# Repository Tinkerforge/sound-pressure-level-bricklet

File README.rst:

Sound Pressure Level Bricklet
=============================

This repository contains the firmware source code and the hardware design
files. The documentation generator configs can be found at
https://github.com/Tinkerforge/generators

Repository Content
------------------

software/:
 * examples/: Examples for all supported languages
 * build/: Compiled files
 * src/: Source code of firmware
 * Makefile: Makefile to build project

hardware/:
 * Contains KiCad project files and additionally schematics as PDF

datasheets/:
 * Contains datasheets for sensors and complex ICs that are used

Hardware
--------

The hardware is designed with the open source EDA Suite KiCad
(http://www.kicad.org). Before you are able to open the files,
you have to install the Tinkerforge kicad-libraries
(https://github.com/Tinkerforge/kicad-libraries). You can either clone
them directly in hardware/ or clone them in a separate folder and
symlink them into hardware/
(ln -s kicad_path/kicad-libraries project_path/hardware). After that you
can open the .pro file in hardware/ with KiCad and from there view and
modify the schematics and the PCB layout.

Software
--------

If you want to do your own Brick/Bricklet firmware development we highly
recommend that you use our build environment setup script and read the
tutorial (https://www.tinkerforge.com/en/doc/Tutorials/Tutorial_Build_Environment/Tutorial.html).

To compile the C code we recommend you to install the newest GNU Arm Embedded
Toolchain (https://launchpad.net/gcc-arm-embedded/+download).
You also need to install bricklib2 (https://github.com/Tinkerforge/bricklib2).

You can either clone it directly in software/src/ or clone it in a
separate folder and symlink it into software/src/
(ln -s bricklib_path/bricklib2 project_path/software/src/). Finally make sure to
have CMake installed (http://www.cmake.org/cmake/resources/software.html).

After that you can build the firmware by invoking make in software/.
The firmware (.zbin) can then be found in software/build/ and uploaded
with brickv (click button "Flashing" on start screen).

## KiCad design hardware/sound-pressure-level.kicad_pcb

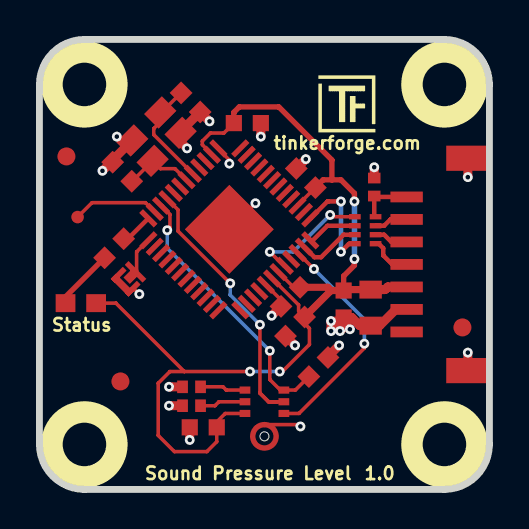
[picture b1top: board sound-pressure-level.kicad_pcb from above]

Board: 2 copper layers, 25.0 x 25.0 mm, 31 parts (2 on the bottom side), 21 nets.

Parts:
C1: 10uF; C0805
C2: 1uF; C0603F
C3, C4, C5, C10: 100nF; C0603F
C6: 220nF; C0603F
C7: 220pF; C0402F
C8, C9: 10pF; C0603F
D3: blue; D0603E
Fiducial_Mark: VAL**; Fiducial_Mark
Fiducial_Mark#2, Fiducial_Mark#3: VAL**; Fiducial_Mark
P1: CON-SENSOR2
P2: BOOT; SolderJumper
P3: DEBUG; DEBUG_PAD
R1: 1k; R0603F
R2: 100k; R0603F
R3, R4: 0; R0402F
RP1: 82; 4X0402
U1: XMC1404; QFN48-EP2
U2, U3, U4, U5: DRILL; DRILL_NP
U6: ICS-43432
VAL: WEEE_7mm
VAL#2: CE_5mm
X1: 16MHz; CRYSTAL_3225

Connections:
GND: C1.1, C2.1, C3.2, C4.2, C5.2, C6.2, C7.2, C8.2, C9.2, C10.1, P1.2, P1.EP, P2.1, R2.2, R3.2, R4.2, U1.17, U1.37, U1.EP, U6.4, X1.3
unnamed: C7.1, P1.7, RP1.4
unnamed: C8.1, U1.41, X1.2
unnamed: C9.1, U1.42, X1.1
unnamed: D3.2, R1.2
unnamed: P1.4, RP1.1
unnamed: P1.5, RP1.2
unnamed: P1.6, RP1.3
unnamed: P2.2, U1.1
unnamed: P3.1, U1.47
unnamed: R1.1, U1.48
unnamed: R3.1, U6.1
unnamed: R4.1, U6.2
S-CLK: RP1.7, U1.23
S-CS: RP1.8, U1.25
S-MISO: RP1.5, U1.20
S-MOSI: RP1.6, U1.24
SCK: U1.45, U6.6
SD: R2.1, U1.46, U6.7
VCC: C1.2, C2.2, C3.1, C4.1, C5.1, C6.1, C10.2, D3.1, P1.3, U1.18, U1.19, U1.27, U1.38, U6.3
WS: U1.22, U6.5

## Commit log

2017-11-14 Add initial schematic
2017-11-14 Add new filtering
2017-11-20 Add datasheet
2017-11-23 Add first version of schematic
2017-11-30 Add capacitors and fix GND net
2017-11-30 Add initial PCB
2017-11-30 Add capacitor for microphone
2017-11-30 Add capacitor for microphone & logos
2018-01-09 add fiducial marks
2018-01-19 add errata
2018-01-22 Remove R9
2018-01-22 Add debug pad
2018-01-26 center microphone, pulldown 100k
2018-01-26 add microphone markings
2018-02-02 Add LUT generator implementation
2018-02-02 Add implementation
2018-02-02 Rename ICS43432 pdf
2018-02-02 Add default gitignore
2018-02-02 Add lut_ prefix for hamming lookup table
2018-02-20 Cleanup KiCad libraries config
    Ensure LibDir=kicad-libraries and LibName1=tinkerforge.
    Remove special library.
2018-03-05 Remove unused flash-size define
2018-03-15 fix logo positions
2018-03-27 specify processor
2018-03-27 fix processor description text layer
2018-03-27 change placement attribute for ics
2018-04-16 Add 3d information (final)
2018-04-16 Add 3d model (*.FCStd & *.step)
2018-05-04 Add schematic PDF
2018-05-04 Rename file
2018-05-18 change series resistor 220 -> 82 ohm
2018-06-04 Disable debugging
2018-06-06 Adapt to bricklib2 callback-value changes to fix wrong length of get-decibel packet
2018-06-07 Update changelog for initial release
2018-06-07 Change pin from test to production version
2018-06-07 Make sure that we can't get into a i2s interrupt deadlock situation
2018-06-11 Fix 3d model
2018-06-25 Fix packet length bug in get_spectrum_callback_configuration function
2018-06-25 Add ref for 2.0.1
2018-06-27 Add examples
2018-06-28 Fix readme
2018-07-11 Add Makefile with docker support
2018-07-11 Remove obsolete generate_makefile scripts
2018-07-11 Update directory structure and build instructions
2018-10-04 Increase version for new release (changes in bricklib2)
2018-10-04 Add rev to changelog
2018-11-06 Add rust examples
2018-11-07 rust: Accept host names for ip connection, fix naming inconsistencies
2018-11-07 rust: Rename callback receivers.
2018-12-14 Add go examples.
2018-12-14 go: Fix printf parameters.
2018-12-18 go: Change import path.
2018-12-18 go: Change import path again.
2018-12-20 rust: Reformat examples.
2019-01-24 mqtt: Add examples.
2019-01-24 mqtt: Fix example header.
2019-01-24 mqtt: Remove executable bit in example permissions.
2019-01-24 go: Minor example fixes.
2019-01-24 mqtt: Minor example fixes.
2019-02-26 Remove superfluous semicolon
2019-03-28 mqtt: Fix whitespace.
2019-05-28 Improve I2S IRQ performance
    Use local pointer to save the time for accessing the struct
2019-08-22 c: Adapt to bindings changes
2020-01-13 examples: Use python3 input instead of python2 raw_input.
2020-01-13 examples: mqtt: Remove trailing whitespace.
2020-08-19 Add uc examples.
2020-08-25 uc: Fix whitespace
2020-08-27 uc: Fix warnings.
2020-09-02 uc: Add example driver note.
2020-10-16 uc: Fix divisor type.
2021-10-25 Update KiCad link
    https://www.kicad.org/blog/2021/10/Avoid-links-to-former-kicad-domain/
2022-04-19 examples: uc: Rename TF_HalContext to TF_HAL.
2022-04-27 uc: Adapt to bindings changes
2022-07-06 Add license files.

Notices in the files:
hardware/sound-pressure-level.kicad_pcb:
Licensed under CERN OHL v.1.1
Copyright (©) 2018, L.Lauer
Copyright Tinkerforge GmbH 2018.
This documentation describes Open Hardware and is licensed under the
CERN OHL v. 1.1.
